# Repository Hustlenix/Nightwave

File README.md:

# Nightwave

Current builder boundary (2026-10-06): target PCB <=90x60 mm, finished device
about <=110x70x25 mm, INR15,000 electronics + PCB/assembly excluding tools.
Final PCB redesign/routing and enclosure CAD are builder-authored. The large
AI reference is not the final design; battery remains unselected. See
[compact requirements](docs/compact-builder-constraints.md), which supersede
older size/budget and final-CAD authoring permissions below.

## PCB checkpoint - 2026-10-06

The AI-authored [KiCad reference project](hardware/kicad/nightwave-reference/README.md)
now has a routed four-layer board, 132 circuit footprints plus three M2
mounting holes, numbered GPIO assignments, and native manufacturing review
exports. See its [validation status](hardware/kicad/nightwave-reference/VALIDATION_STATUS.md)
and [engineering checkpoint](docs/reference-pcb-checkpoint.md) for exact results.
The [downloadable review package](hardware/kicad/Nightwave-AI-Reference-2026-10-06.zip)
includes editable sources, PDF, Gerbers, drill, positions and board STEP.

The [completion ledger](docs/design-completion-status.md) tracks open work.
The [reference firmware profile](docs/reference-board-firmware.md) now matches
the PCB GPIO map and implements TFT output and expander buttons. Typed ERC,
DRC and schematic/board parity pass locally; hardware operation remains untested.

**This is not fabrication or grant-submission approval.** USB source-current
and protection, power-loop/current capacity, complete component procurement,
firmware-to-board integration and enclosure fit remain unresolved. Clean
connectivity/clearance checks are not electrical safety or functional proof.
The builder requested this separate AI-authored reference when their laptop
could not run KiCad; their original starter files remain untouched.

Nightwave is an in-progress, standalone pocket music player for the Pixl “A Music player for the saloon” Trial. It reads user-owned MP3 and PCM/WAV files directly from microSD, with software decoding, physical controls, wired stereo headphones, a speaker, synchronized LRC and Bluetooth output. No phone or streaming service is required. The builder selected ESP32-S3 plus BM83SM1-00TA (BD-14) and Waveshare 24382 non-touch TFT (BD-15). Their hardware drivers, combined GPIO map and battery sizing are not qualified or locked.

> Status (2026-10-03): WAV/MP3 three-task streaming, bench OLED/five-button interaction,
> lyrics/metadata/M3U, modes, bounded seek/resume, sleep timer and versioned
> persistence are implemented for the provisional hardware. The 2026-10-02
> continuation adds an idle-built SD catalog, paged songs/artists/albums and
> bounded PSRAM lookups for filtered browsing/track changes, MP3 duration/sparse
> seek, full-text display interface, BT/power contracts and engineering telemetry;
> [catalog limits](docs/library-index.md) remain explicit. See the
> [expanded-scope checkpoint](docs/engineering-budgets.md) for remaining software.
> Executed [firmware/host CI evidence](docs/software-validation.md) is revision-specific.
> **Funding package is NOT READY:** final power design,
> complete procurement BOM, reviewed enclosure CAD and human reviews are
> missing. An [AI-authored PCB reference](hardware/kicad/nightwave-reference/README.md)
> now exists; its native checks do not constitute fabrication approval or builder authorship.
> No physical playback, runtime, fit, final hardware or tier is claimed.

## Why it exists

The original hardware workflow used builder-authored mentor/reviewer mode;
the separate AI-authored reference above was subsequently requested. **Before
final schematic tasks**, review the selected [Bluetooth architecture](docs/bluetooth-architecture.md)
and [display BD-15](docs/display-selection.md). BD-16 selects
[TCA9535PWR input expansion](docs/input-expansion.md); review its [combined GPIO map](docs/pin-budget.md)
and review the [current power model](docs/current-power-model.md), charger/pack
and complete BOM before the first schematic task. Then use
[builder tasks](docs/builder-tasks.md), [subsystem requirements](docs/schematic-requirements.md)
and [your decision log](docs/builder-decisions.md). AI research and review are
disclosed; final schematic, routing and enclosure must be materially authored
by the builder. The reported Pixl clarification does not mark missing work done.

The product goal is to play the builder's own music offline without a phone,
notifications, subscription or hidden playback module. The builder's personal
motivation and genuine work journal must remain their own account; this README
does not invent a first-person build story.

## Architecture

```text
microSD / FAT
      |
      v
StorageTask -> compressed ring buffer -> DecoderTask -> PCM ring buffer
                                                        |
                                                        v
                                                AudioOutputTask
                                                        |
                                                   I2S + DMA
                                      +-----------------+-----------------+
                                      |                                   |
                                PCM5102A DAC                       MAX98360C amp
                                      |                                   |
                              TPA6132A2 headphone amp                mono speaker
                                      |
                               3.5 mm stereo jack
```

The ESP32 owns file enumeration, storage reads, MP3/WAV decoding, buffering, playback state, I2S output, buttons, UI, settings, diagnostics, and power policy. Nightwave does not use DFPlayer or another module that hides the storage/decode/playback pipeline. The diagram above is the current two-local-output software/bench path. The product requires a third mutually exclusive, rate-qualified I2S branch to BM83SM1-00TA for A2DP source output. Its radio adapter, combined playback router and 22.05/32 kHz conversion are not implemented. Host-tested Bluetooth control/framing contracts do not make that output operational.

The bench prototype uses an available MAX98357A breakout as a functional speaker-path proxy. The current AI-authored KiCad reference uses MAX98357AETE+T (TQFN); MAX98360C in historical candidate documents is not the reference board's fitted amplifier. This remains an unqualified engineering candidate.

## Current implementation

- repository and required engineering-document structure;
- current Pixl/Trial rules verification and honest AI-disclosure strategy;
- datasheet-backed provisional component comparison, BOM, pin budget, power tree, risk register, prototype plan, and decoder study;
- ESP-IDF 6.1 C++ firmware with safe-muted boot, chip/reset/heap/PSRAM diagnostics, debounced five-button logging, 1-bit SDMMC mount/enumeration/benchmarking, I2S DMA output, and a low-level tone test;
- robust host-tested WAV parsing for 16-bit mono/stereo PCM at 22.05/32/44.1/48 kHz, including unknown-chunk skipping and explicit errors;
- three-task WAV/MP3 streaming through a 32 KiB encoded ring and 16,384-frame
  SPSC PCM ring, pause/resume, cancellation, gain ramps and queue/error telemetry;
- SH1106 OLED driver (SSD1306 option), file/folder browser, now-playing, five
  buttons, headphone indicator, no-SD/error screens, sleep and diagnostics;
- bounded LRC, ID3v2.3/v2.4/ID3v1/WAV INFO metadata and local M3U/M3U8 loading;
- SD-backed incremental catalog, 16-row songs/artists/albums views, full indexed
  collection/filter queues, bounded artist/album lookup and checked ordinal-hint
  filter/folder resume; low-memory/over-cap caches use a slower fallback;
- normal/shuffle/repeat-all/repeat-track; accepted-sample lyric clock; WAV direct
  seek and idle-built sparse MP3 seek checkpoints with decoder preroll, safe
  decode-from-start fallback and a 30-minute resume/seek cap;
- versioned checked NVS volume/mode/output/resume/playlist/folder persistence,
  explicit saved-track resume and 15/30/45/60-minute/end-track sleep timers;
- JSON boot/stream/performance/self-test/engineering records, with unmeasured hardware marked;
- injected display frame interface carrying full bounded metadata/LRC strings;
  tested Bluetooth source-state/timeout/backpressure boundary and unknown-safe
  power HAL, without pretending unqualified adapters are operational;
- portable tests for WAV parsing, generated fixtures, ring wrap/full behavior, stereo-to-mono arithmetic, volume scaling, button debounce, and playback state;
- CI definitions for both ESP32-S3 firmware and portable host tests;
- exact Phase 2 prototype BOM, pin-by-pin wiring table, voltage/current plan, deterministic test-media generator, and staged bring-up checklist.

The firmware does **not** prove that a card mounts, a waveform reaches a physical
module, a speaker/headphone produces correct audio, or buffering survives real
card latency. OLED/controller wiring, jack detection and NVS behavior still need
bench validation. Battery reads, power-latch shutdown and automatic SD hotplug
reinitialization are not implemented. Retry/error handling is not a claim that
removing a real card during playback has been tested.

## Controls

The [Trial acceptance matrix](docs/trial-acceptance.md) maps every requirement to
source and missing physical proof. The [runtime recorder](docs/runtime-test.md)
logs sampled elapsed/playback windows and faults; it cannot certify battery life.

Previous/Next navigate the browser or change playing tracks. Play opens a folder
or starts/toggles playback. Volume +/- changes gain. Hold Play for the browser,
hold Previous for the parent folder, hold Volume + for diagnostics, hold Next
for lyrics and hold Volume - for mode/sleep/resume/output settings. First input
after the 30 s display sleep wakes without changing playback.
See [complete controls and limitations](docs/player-controls.md).

## Audio architecture

Helix decodes MP3 in software on ESP32-S3; WAV uses the validated PCM parser.
Storage, decode and I2S have separate tasks. PCM is stereo 16-bit at supported
22.05/32/44.1/48 kHz rates. ID3 skipping and resynchronization are bounded;
unsupported or corrupt media produces a recoverable error. The Class-D path
must select averaged-stereo mono in the reviewed final hardware; headphone
output uses the separate stereo DAC/amp path. Neither path is physically proven.

## Power architecture

USB-C and a protected 1S pack feed a charger/power path; SYS powers the speaker
and a buck-boost supplies 3.3 V. This direction is **provisional**, not a finished
circuit. The [selected-product screening model](docs/current-power-model.md)
calculates MCU, SD, selected TFT, speaker/wired/BT, idle, transients and charging.
Its continuously lit typical speaker case needs an estimated 7.08 Ah for eight
hours under the documented margins; a hypothetical 6.6 Ah gives 7.46 h, not a
passing measurement. Dimming/gating scenarios are conditional, not implemented
power savings. The [historical OLED model](docs/power-budget.md) is superseded.
[Charger timer, source-current and peak-load conflicts](docs/power-assumptions.md)
must be resolved before locking hardware. Estimated runtime is not measured
runtime, and charge-while-play safety is not verified.

## PCB and enclosure

The [current KiCad reference](hardware/kicad/nightwave-reference/README.md)
contains a seven-sheet schematic, placed four-layer board, project-local land
patterns and explicit pin map. Check its [revision-specific validation status](hardware/kicad/nightwave-reference/VALIDATION_STATUS.md)
for actual routing, DRC/parity results and available review exports. The source
is AI-authored at the builder's request, not evidence of human-authored CAD.
It is not fabrication approved. No reviewed editable enclosure, full mechanical
assembly or physical build proof is claimed. See [the reference differences and remaining gates](docs/reference-pcb-checkpoint.md).
An [AI-assisted KiCad starter](hardware/kicad/nightwave-starter/START_HERE.md)
now supplies a root hierarchy, six empty subsystem sheets and a blank board so
the builder can begin quickly. It is scaffolding only: it contains no finished
circuit, footprint assignment, GPIO map, placement or routing and is not funding
evidence by itself.
The board, battery, speaker, display, controls and ports must all have verified
mounting and clearances in the builder-owned design before funding submission.

## BOM

[Preliminary BOM CSV](hardware/BOM.csv): captured-price core subtotal **$53.16**,
including selected BM83 and Waveshare 24382, excluding the pending battery. This is
not a finished BOM total or funding/order cost. USB-C, support parts, PCB,
assembly, enclosure, delivery and taxes also remain excluded/pending. Critical
rows now include package, datasheet, source, footprint and electrical roles;
pending rows are explicit, not approved substitutes. The spreadsheet review
preserved the CSV and checked its selected/pending fields. Older prices remain
dated snapshots; the selected display was checked via official indexed content
2026-10-03 (direct fetch refused; stock/delivery unverified).
No parts have been ordered by this run.

## Build the firmware

Target toolchain: ESP-IDF `v6.1`, target `esp32s3`.

```sh
cd firmware
idf.py set-target esp32s3
idf.py build
```

The development baseline is `ESP32-S3-DevKitC-1-N8R8`; the provisional final module is `ESP32-S3-WROOM-1-N16R8`. Pins and component choices remain provisional until prototype validation.

Use `idf.py -p PORT flash monitor` after building, with the documented DevKit
only and verified wiring. The console adds `play`, `pause`, `resume`, and
`volume` to the bench commands; `wav` remains an alias. Follow
[Phase 3 firmware bring-up](docs/phase3-firmware-bringup.md) before enabling an
output. Production flashing/power instructions depend on the unfinished PCB.

## Load music and build the prototype

Copy supported `.wav` or `.mp3` files to a FAT-formatted microSD, optionally in
folders. Paths must be under 256 bytes; the browser displays at most 128 entries
per folder. No streaming or network is used. Generated test tones are described
in [test media](docs/test-tracks.md). Free-format/MPEG2.5 MP3, unsupported rates,
24-bit WAV and full Unicode display are not implemented features. Bounded WAV
and MP3 seek and shuffle are implemented; their limits and fallback behavior are
documented in [player controls](docs/player-controls.md) and [software evidence](docs/software-validation.md).

For the USB-powered human-assembled prototype, use the
[prototype BOM](hardware/prototype-BOM.csv), [wiring](docs/prototype-wiring.md)
and [bring-up checklist](docs/prototype-bringup.md). Do not connect a lithium
pack or place a final-PCB order using this preliminary package.

## Current validation and funding status

[Software evidence](docs/software-validation.md) separates actual CI runs from
host simulations and pending board measurements. The regression suite exercises
1000 start/cancel/control transitions, corrupt media, fragmented MP3, WAV,
concurrent ring transfers and real folder-navigation logic with fake devices.

[Funding audit](docs/funding-readiness.md),
[current official requirements](docs/pixl-funding-readiness.md),
[builder design/provenance review](docs/human-design-review.md), and
[independent sanity-check packet](docs/sanity-check.md) record the exact gaps.
Project 1200 was inspected in the authenticated builder session on 2026-10-02.
It is a hardware funding draft, with finished-build status unchecked. The Trial
requires local files, real speakers, physical playback/volume controls and a
full-night battery with the achieved runtime stated. Design funding and finished
build evidence are separate stages; see [the current project audit](docs/project-1200-audit.md).
No funding request has been submitted.

Run the [shipping artifact inventory](docs/shipping-audit.md) to expose unresolved
costs and missing design sources. A passing development validator or green form
checkbox does not establish a complete funding design or T4 eligibility.

## Finished-device acceptance

The [finished-device evidence inventory](docs/trial-acceptance.md#finished-device-evidence-inventory)
tracks own-file standalone speaker playback, physical play/pause/skip/volume,
actual full-night speaker battery runtime, final schematic/CAD/STEP, parts/build
instructions, build photos and a real demo video. The pending record is
[trial-evidence.json](measurements/trial-evidence.json); **achieved runtime is
unknown**, not an estimate or a simulated eight-hour result. No demo video exists
yet. Only populate evidence after the corresponding real work and human review.

```sh
python3 tools/check_trial_readiness.py
```

Exit 2 lists missing evidence. Exit 0 only inventories builder-reported evidence
for human review; it never certifies playback, safety, runtime, authorship or Pixl
acceptance. Keep the full [systems scope](docs/trial-acceptance.md) through release;
the hardware integrations must work, not just appear in the feature list.

## Engineering documents

- [Pixl requirements](docs/pixl-requirements.md)
- [Architecture notes](docs/architecture-notes.md)
- [Component comparison](docs/component-comparison.md)
- [Decoder study](docs/decoder-study.md)
- [Decision log](docs/decisions.md)
- [Pin budget](docs/pin-budget.md)
- [Power tree](docs/power-tree.md)
- [Prototype plan](docs/prototype-plan.md)
- [Prototype BOM](hardware/prototype-BOM.csv)
- [Prototype wiring](docs/prototype-wiring.md)
- [Prototype bring-up checklist](docs/prototype-bringup.md)
- [Deterministic test media](docs/test-tracks.md)
- [Phase 3 firmware bring-up](docs/phase3-firmware-bringup.md)
- [Audio buffer analysis](docs/audio-buffer-analysis.md)
- [Headphone prototype options](docs/headphone-prototype-options.md)
- [MP3 integration plan](docs/mp3-integration-plan.md)
- [Risk register](docs/risks.md)
- [Preliminary BOM](hardware/BOM.csv)
- [AI disclosure](docs/ai-disclosure.md)

## Physical validation still required

Direct-SD playback, decoder timing, buffer sizing, audio quality, channel correctness, output power, noise, thermal behavior, current draw, charge-while-play behavior, battery capacity, full-night runtime, PCB manufacturability, and enclosure fit all require physical evidence. The project-defined acceptance test is at least eight hours of continuous speaker playback under a declared profile; the current Pixl Trial itself says “a full night” and requires the achieved runtime to be stated, but does not publish an exact hour count.

## AI disclosure

AI assistance is being used for research synthesis, repository scaffolding, interface design, documentation, and software checks. The builder must understand and materially review the electrical and mechanical design, physically assemble and test the device, maintain honest journals and photos, and obtain a second-person sanity check before hardware submission. Fully AI-generated hardware design files are not acceptable under the current Pixl hardware rules.

## License

Nightwave's original repository content is provided under the MIT License. Third-party libraries keep their own licenses and notices.
The MP3 wrapper's Apache-2.0 license does not relicense the RealNetworks Helix
decoder. Read [dependency provenance and terms](docs/decoder-licenses.md);
notices are preserved in [licenses](licenses/). Original tone fixtures and the
small text font are generated within this repository, not downloaded media.

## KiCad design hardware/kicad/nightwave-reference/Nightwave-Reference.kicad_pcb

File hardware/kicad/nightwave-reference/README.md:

# Nightwave KiCad reference design

This directory is an AI-authored KiCad engineering reference. See `VALIDATION_STATUS.md` for the actual routing/check results of the exported revision. It is unbuilt, unmeasured, and **not approved for fabrication or lithium-cell connection**. It is not evidence of human-authored CAD or Pixl acceptance.

## What is here

- native KiCad 10 hierarchical schematic and four-layer PCB source;
- selected ESP32-S3, BM83, Waveshare TFT, TCA9535, local DAC/headphone/speaker, USB-C, charger, dual regulated rails, protected battery and service/test interfaces;
- exact logical net/GPIO assignments generated from the same source as the PCB;
- BOM and machine-readable design manifest;
- `manufacturing/` review exports generated by KiCad CLI and prominently marked **DO NOT FABRICATE**;
- `reports/` ERC/DRC/netlist and rendered-review evidence.

## Critical stop

Do not order this board yet. An independent reviewer must close `REVIEW_CHECKLIST.md`. Automated routing and clearance/connectivity checks do not establish USB impedance, power-loop stability, current capacity, RF performance, charger safety, manufacturability or enclosure fit. IC pins now have explicit electrical types from manufacturer pin-function tables. ERC checks this model; it does not verify analog behavior or mode-dependent module configuration. The four source flags declare external power/ground and the analog rail after R30, not safety approval.

## Opening tomorrow

Open `Nightwave-Reference.kicad_pro`. Start with the root schematic, then inspect the PCB. The existing `nightwave-starter` project is intentionally separate and unchanged.

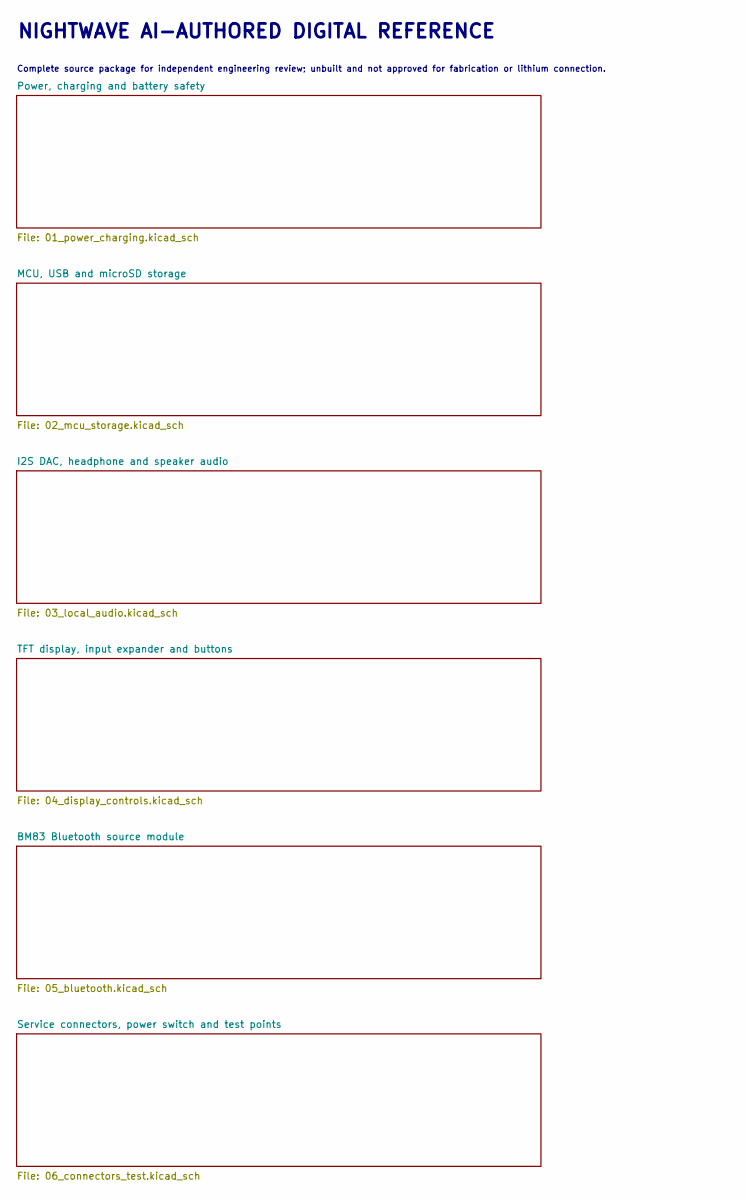
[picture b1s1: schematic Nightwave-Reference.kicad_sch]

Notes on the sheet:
NIGHTWAVE AI-AUTHORED DIGITAL REFERENCE
Complete source package for independent engineering review; unbuilt and not approved for fabrication or lithium connection.

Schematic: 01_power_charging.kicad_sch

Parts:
C1, C2, C7: 10u; C_0603_1608Metric
C3, C4, C5, C6: 22u; C_0603_1608Metric
C8: 4.7u; C_0603_1608Metric
C9: 47n/10V; C_0805_2012Metric
C10: 10u/25V; C_0805_2012Metric
C11, C13: 10u/10V; C_0805_2012Metric
C12, C14: 22u/10V; C_0805_2012Metric
C15: 100n/10V; C_0805_2012Metric
J1: USB4105-GF-A; USB_C_Receptacle_GCT_USB4105-xx-A_16P_TopMnt_Horizontal
J2: BATTERY_CONNECTOR; JST_PH_S2B-PH-K_1x02_P2.00mm_Horizontal
J3: EXTERNAL_10K_NTC; JST_PH_S2B-PH-K_1x02_P2.00mm_Horizontal
L1, L2: 0.47uH XFL4015-471MEC; Coilcraft_XFL4015
L3: 0.7uH XFL4015-701MEC; Coilcraft_XFL4015
R1, R2: 5.1k; R_0603_1608Metric
R3, R4: 4.7k; R_0603_1608Metric
R16: 511k; R_0603_1608Metric
R17, R19: 91k; R_0603_1608Metric
R18: 562k; R_0603_1608Metric
R20: 5.49k; R_0603_1608Metric
R21: 5.23k; R_0603_1608Metric
R22: 30.1k; R_0603_1608Metric
R23: 0; R_0603_1608Metric
U3: BQ25628ERYKR; TI_RYK0018A
U4: TPS22965DSGR; Texas_DSG0008A_WSON-8-1EP_2x2mm_P0.5mm_EP0.9x1.6mm_ThermalV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
U5, U6: TPS63802DLAR; TI_DLA0010A
U7: MAX17048G+T10; TDFN-8-1EP_2x2mm_P0.5mm_EP0.8x1.2mm

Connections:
+3V3: C5.1 (+3V3), C12.1 (+3V3), R3.2 (+3V3), R4.2 (+3V3), R16.1 (+3V3), U5.6 (VOUT); also elsewhere on the board
+3V3_A: C7.1 (+3V3_A); also elsewhere on the board
+3V6_BT: C6.1 (+3V6_BT), C14.1 (+3V6_BT), R18.1 (+3V6_BT), U6.6 (VOUT); also elsewhere on the board
BAT: C2.1 (BAT), C15.1 (BAT), J2.1, U3.8 (BAT), U7.2 (CELL), U7.3 (VDD); also elsewhere on the board
BTST: C9.1 (BTST), U3.1 (BTST)
CHASSIS: J1.SH (SHIELD), R23.1 (CHASSIS)
CHG_INT_N: U3.11 (INT); also elsewhere on the board
CHG_STAT: U3.10 (STAT); also elsewhere on the board
FB_3V3: R16.2 (FB_3V3), R17.1 (FB_3V3), U5.4 (FB)
FB_BT: R18.2 (FB_BT), R19.1 (FB_BT), U6.4 (FB)
FUEL_ALERT_N: U7.5 (ALRT); also elsewhere on the board
GND: C1.2 (GND), C2.2 (GND), C3.2 (GND), C4.2 (GND), C5.2 (GND), C6.2 (GND), C7.2 (GND), C8.2 (GND), C10.2 (GND), C11.2 (GND), C12.2 (GND), C13.2 (GND), C14.2 (GND), C15.2 (GND), J1.A1 (GND), J1.A12 (GND), J1.B1 (GND), J1.B12 (GND), J2.2, J3.2, R1.2 (GND), R2.2 (GND), R17.2 (GND), R19.2 (GND), R20.2 (GND), R22.2 (GND), R23.2 (GND), U3.14 (CE), U3.15 (GND), U4.5 (GND), U4.9 (EP), U5.2 (MODE), U5.3 (AGND), U5.8 (GND), U6.2 (MODE), U6.3 (AGND), U6.8 (GND), U7.1 (CTG), U7.4 (GND), U7.6 (QSTRT), U7.9 (EP); also elsewhere on the board
I2C_SCL: R4.1 (I2C_SCL), U3.13 (SCL), U7.7 (SCL); also elsewhere on the board
I2C_SDA: R3.1 (I2C_SDA), U3.12 (SDA), U7.8 (SDA); also elsewhere on the board
ILIM: R20.1 (ILIM), U3.4 (ILIM)
PGOOD_CHG: U3.3 (PG); also elsewhere on the board
PMID: C10.1 (PMID), U3.17 (PMID)
PWR_GOOD_3V3: U5.5 (PG); also elsewhere on the board
PWR_GOOD_BT: U6.5 (PG); also elsewhere on the board
PWR_SWITCH_ON: U4.3 (ON); also elsewhere on the board
REGN: C8.1 (REGN), U3.2 (REGN)
SW1_3V3: L1.1, U5.9 (L1)
SW1_BT: L2.1, U6.9 (L1)
SW2_3V3: L1.2, U5.7 (L2)
SW2_BT: L2.2, U6.7 (L2)
SW_CHG: C9.2 (SW_CHG), L3.1, U3.16 (SW)
SYS: C3.1 (SYS), L3.2, U3.9 (SYS), U4.1 (VIN), U4.2 (VIN), U4.4 (VBIAS); also elsewhere on the board
TS: J3.1, R21.2 (TS), R22.1 (TS), U3.6 (TS)
TS_BIAS: R21.1 (TS_BIAS), U3.5 (TS_BIAS)
USB_CC1: J1.A5 (CC1), R1.1 (USB_CC1)
USB_CC2: J1.B5 (CC2), R2.1 (USB_CC2)
USB_DM: J1.A7 (D-), J1.B7 (D-); also elsewhere on the board
USB_DP: J1.A6 (D+), J1.B6 (D+); also elsewhere on the board
VBUS5: C1.1 (VBUS5), J1.A4 (VBUS), J1.A9 (VBUS), J1.B4 (VBUS), J1.B9 (VBUS), U3.18 (VBUS); also elsewhere on the board
VSYS_SW: C4.1 (VSYS_SW), C11.1 (VSYS_SW), C13.1 (VSYS_SW), U4.7 (VOUT), U4.8 (VOUT), U5.1 (EN), U5.10 (VIN), U6.1 (EN), U6.10 (VIN); also elsewhere on the board

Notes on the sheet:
Power, charging and battery safety
AI-authored engineering reference. Verify pinout, support values, footprint orientation, lithium safety, RF keepout and assembly before fabrication.

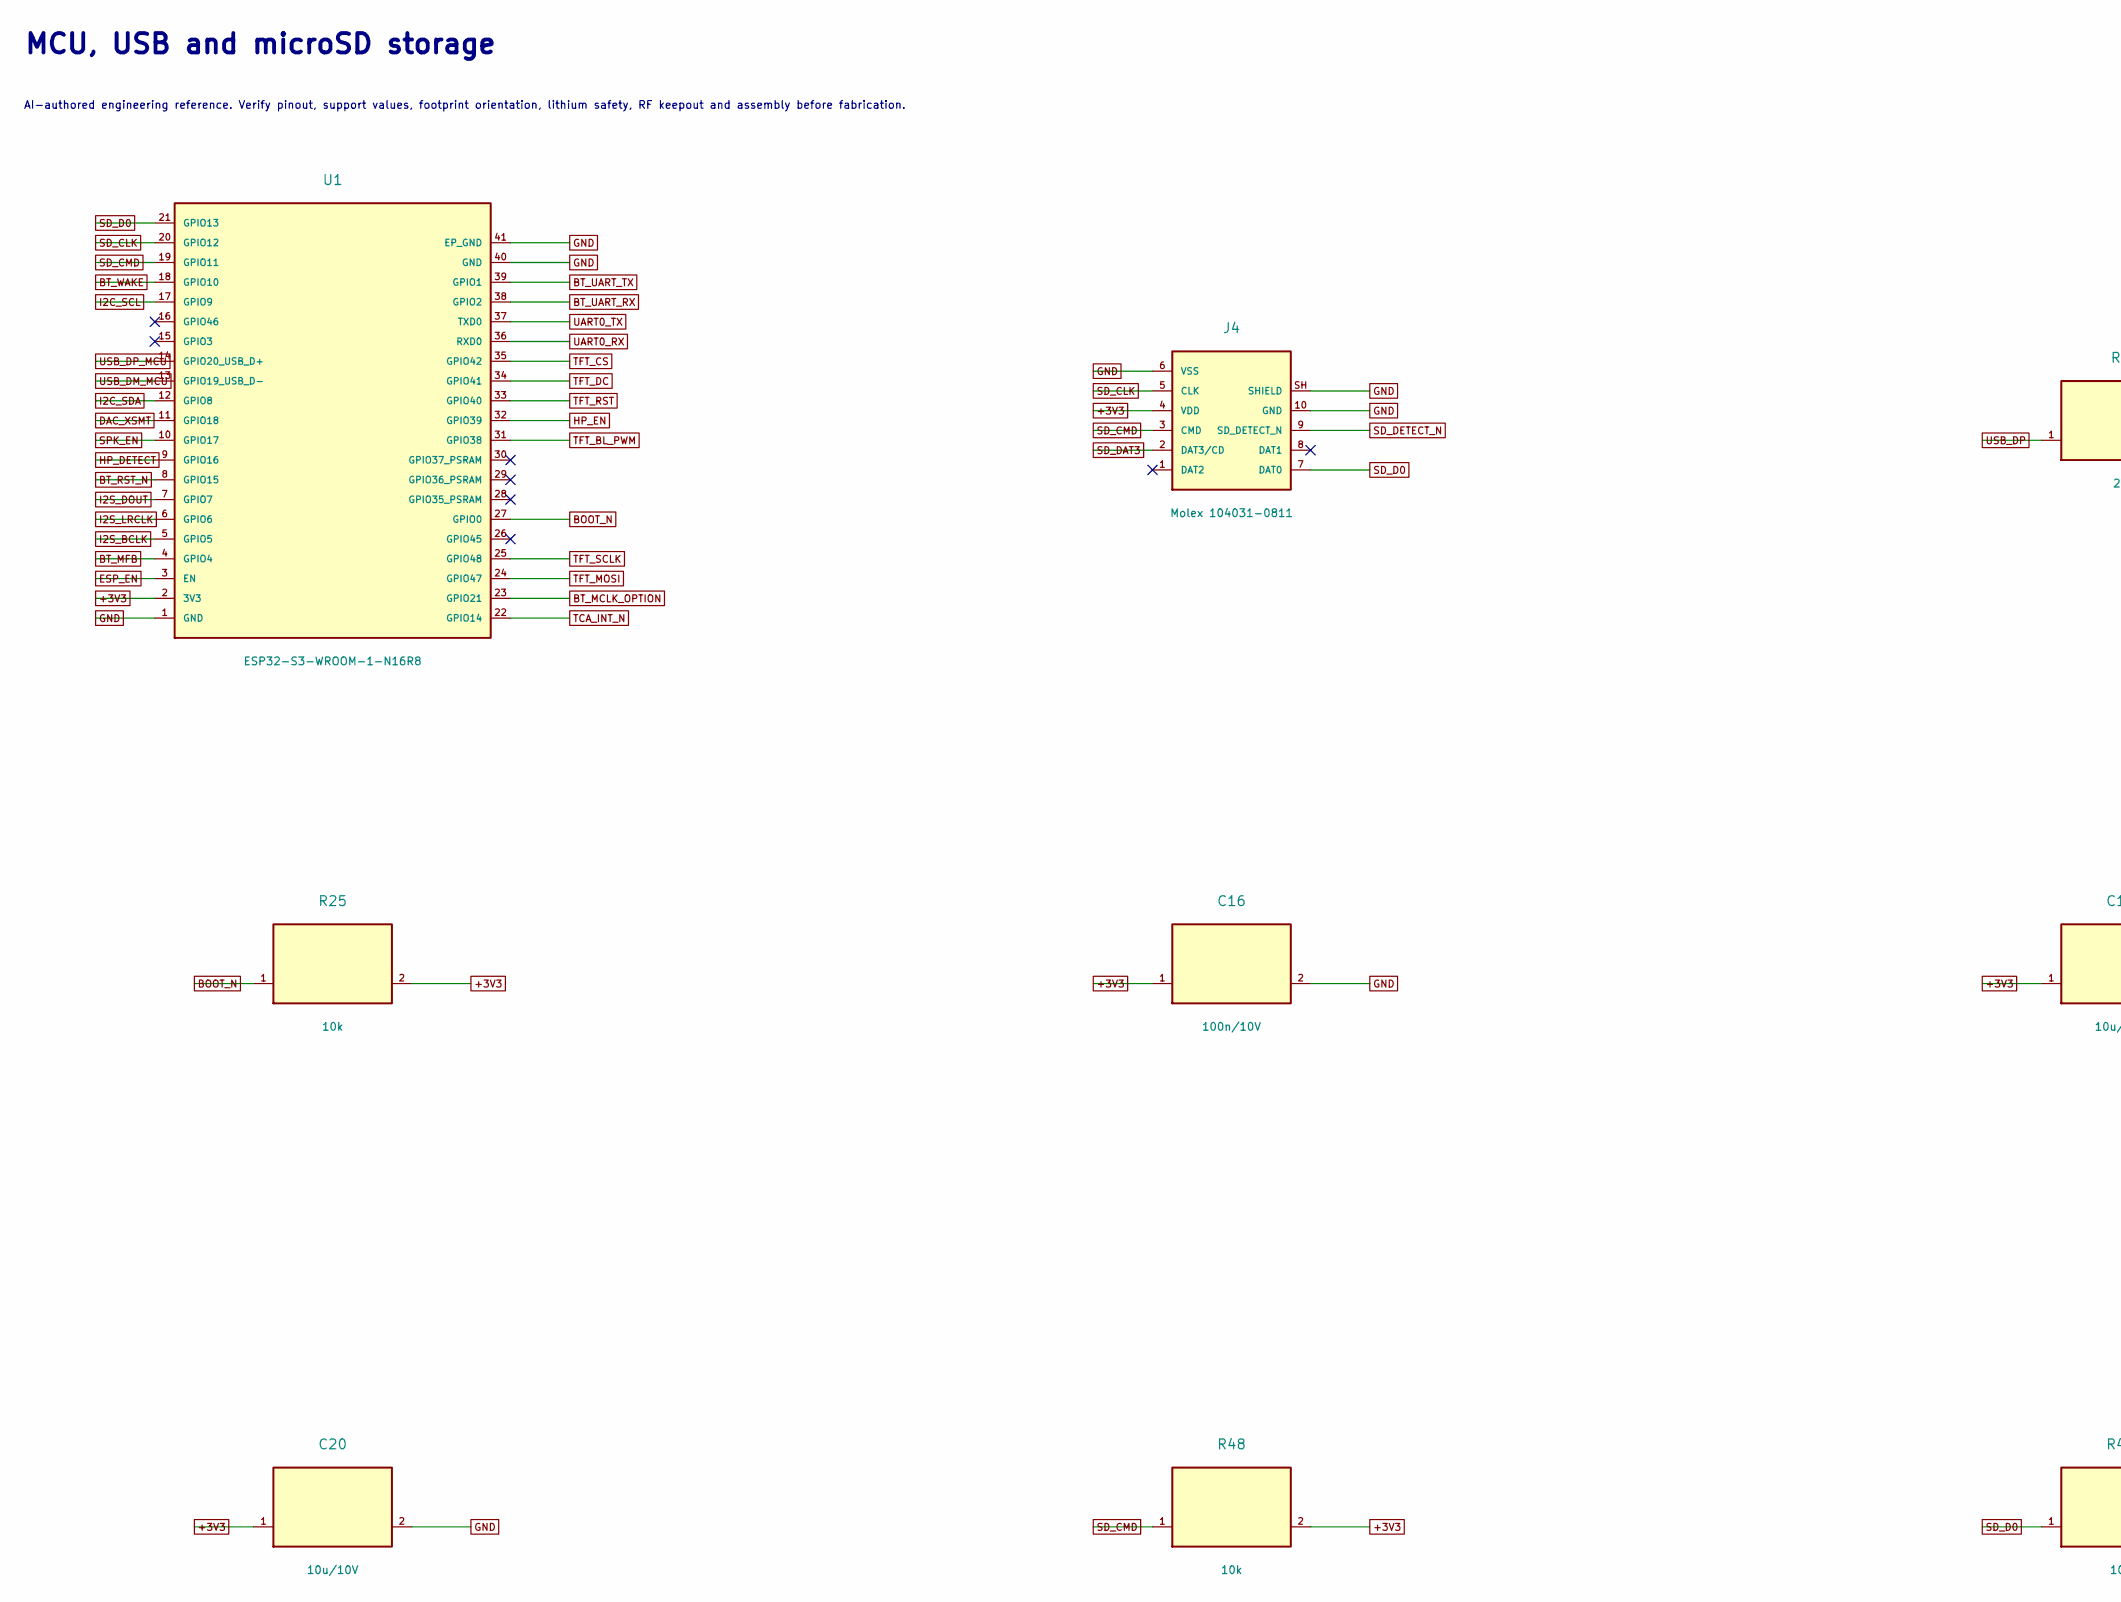
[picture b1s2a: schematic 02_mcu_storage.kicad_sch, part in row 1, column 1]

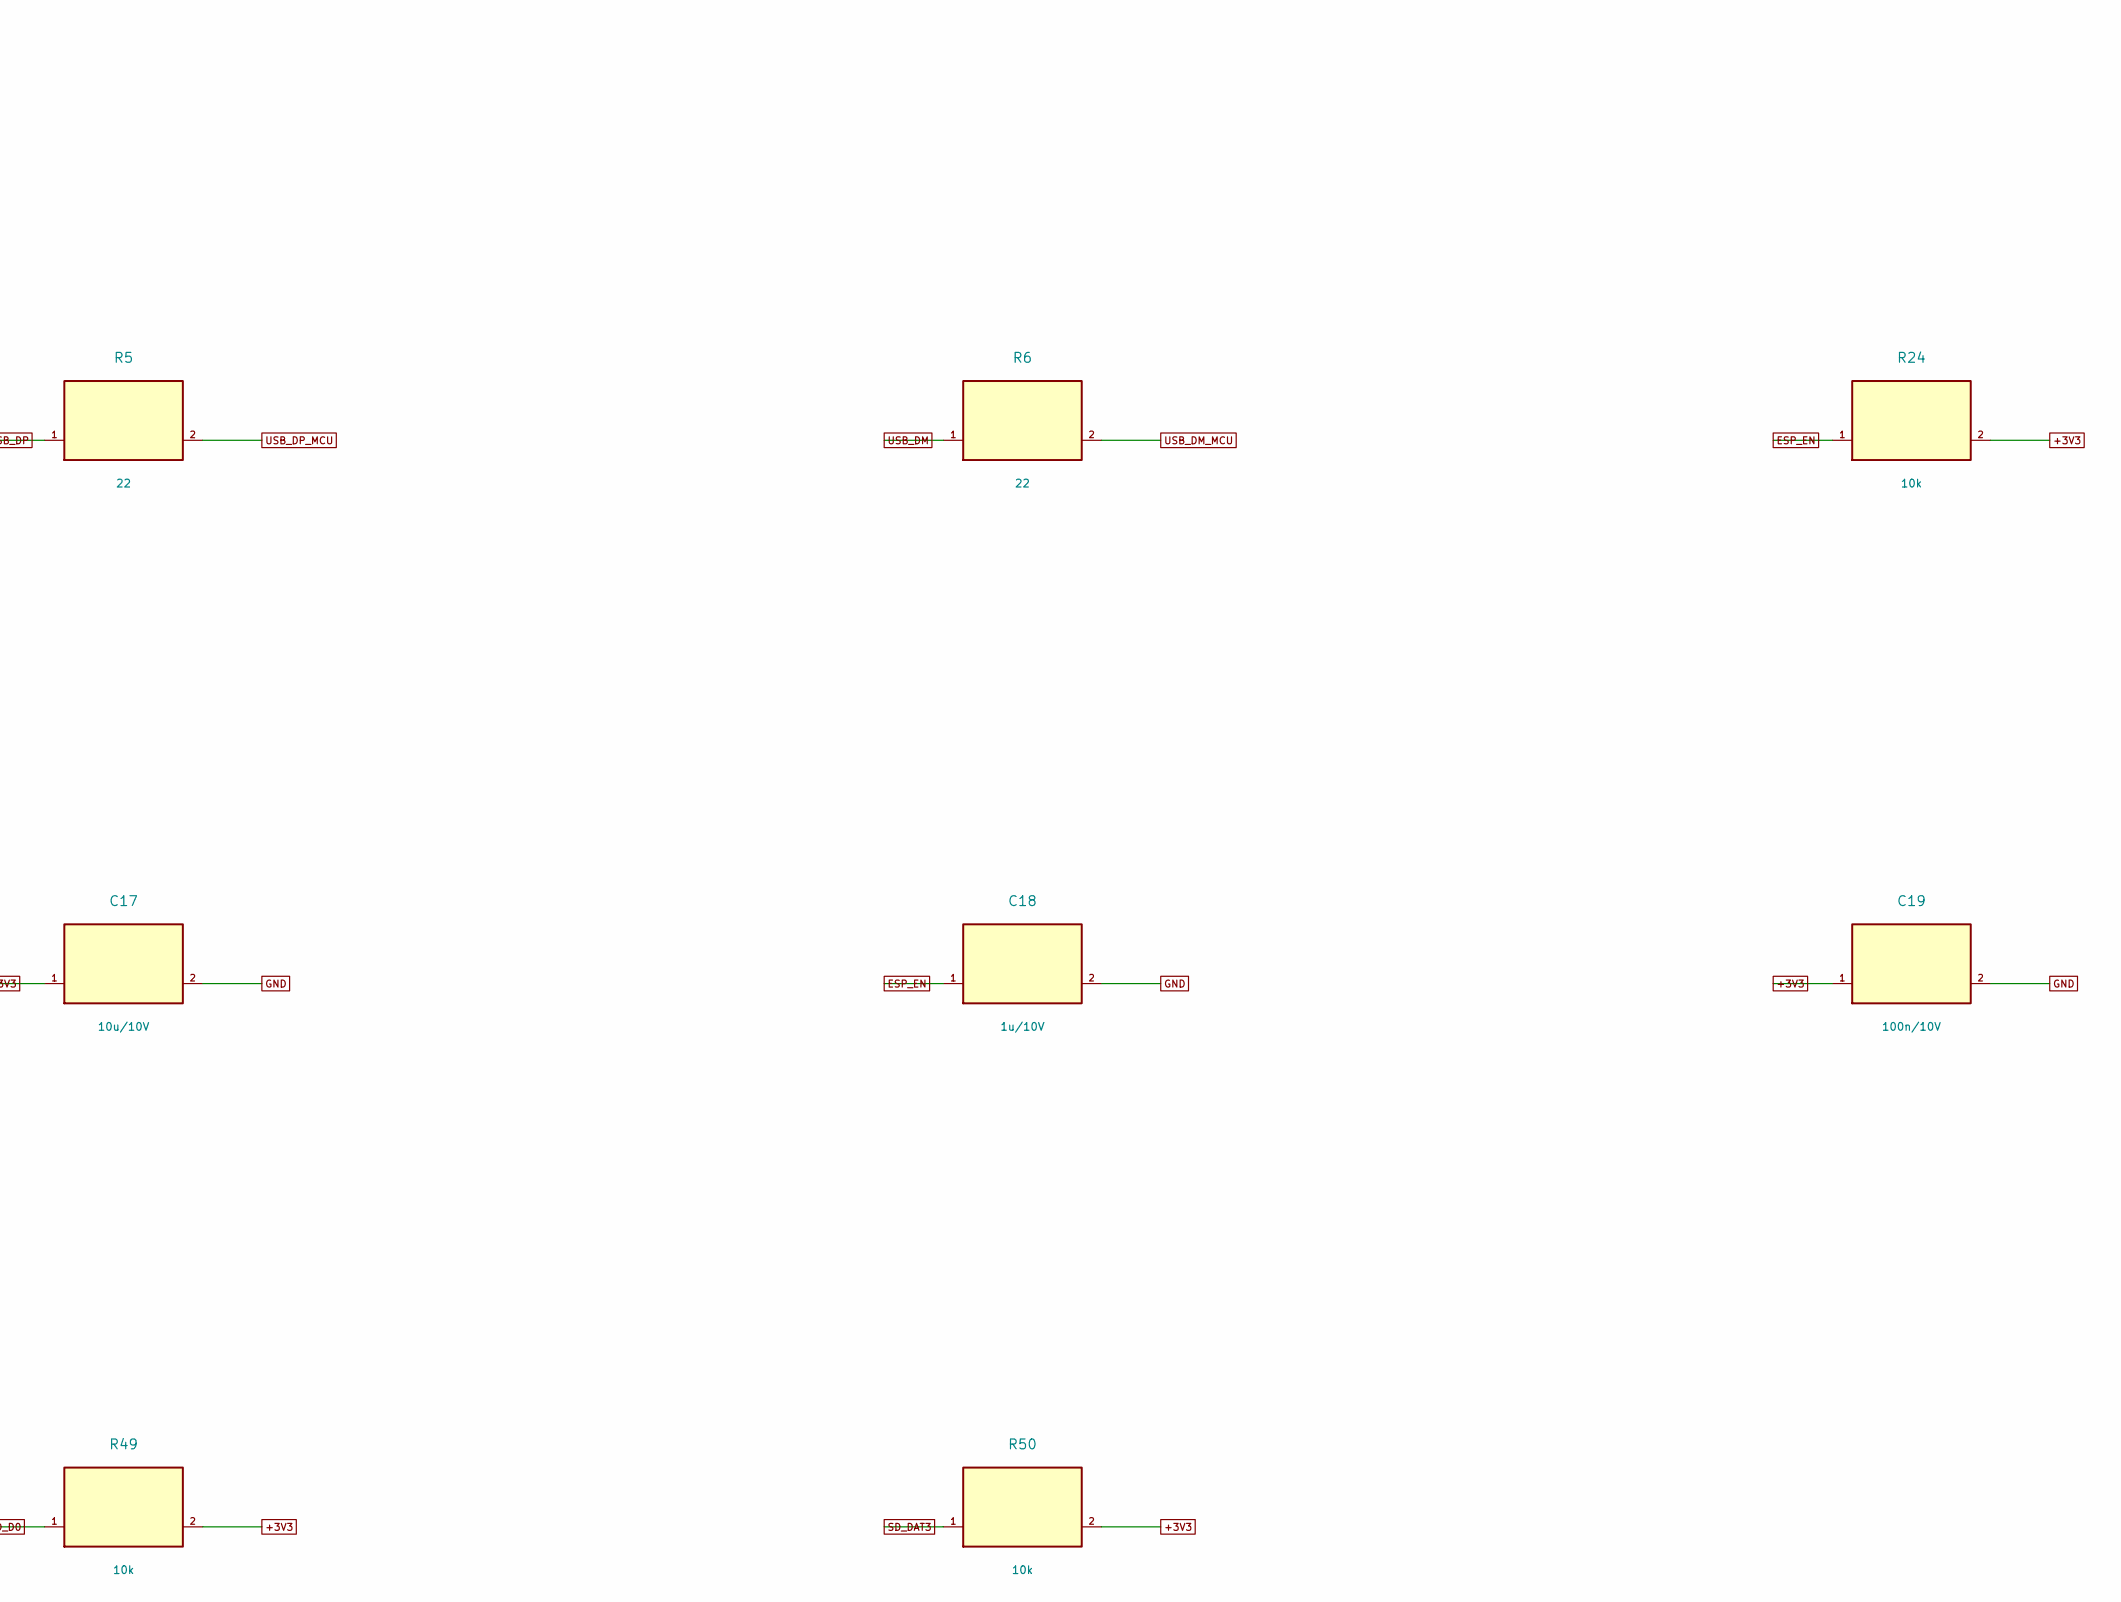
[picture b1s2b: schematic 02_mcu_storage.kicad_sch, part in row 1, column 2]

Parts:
C16, C19: 100n/10V; C_0805_2012Metric
C17, C20: 10u/10V; C_0805_2012Metric
C18: 1u/10V; C_0805_2012Metric
J4: Molex 104031-0811; microSD_HC_Molex_104031-0811
R5, R6: 22; R_0603_1608Metric
R24, R25, R48, R49, R50: 10k; R_0603_1608Metric
U1: ESP32-S3-WROOM-1-N16R8; ESP32-S3-WROOM-1

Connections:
+3V3: C16.1 (+3V3), C17.1 (+3V3), C19.1 (+3V3), C20.1 (+3V3), J4.4 (VDD), R24.2 (+3V3), R25.2 (+3V3), R48.2 (+3V3), R49.2 (+3V3), R50.2 (+3V3), U1.2 (3V3); also elsewhere on the board
BOOT_N: R25.1 (BOOT_N), U1.27 (GPIO0); also elsewhere on the board
BT_MCLK_OPTION: U1.23 (GPIO21); also elsewhere on the board
BT_MFB: U1.4 (GPIO4); also elsewhere on the board
BT_RST_N: U1.8 (GPIO15); also elsewhere on the board
BT_UART_RX: U1.38 (GPIO2); also elsewhere on the board
BT_UART_TX: U1.39 (GPIO1); also elsewhere on the board
BT_WAKE: U1.18 (GPIO10); also elsewhere on the board
DAC_XSMT: U1.11 (GPIO18); also elsewhere on the board
ESP_EN: C18.1 (ESP_EN), R24.1 (ESP_EN), U1.3 (EN); also elsewhere on the board
GND: C16.2 (GND), C17.2 (GND), C18.2 (GND), C19.2 (GND), C20.2 (GND), J4.6 (VSS), J4.10 (GND), J4.SH (SHIELD), U1.1 (GND), U1.40 (GND), U1.41 (EP_GND); also elsewhere on the board
HP_DETECT: U1.9 (GPIO16); also elsewhere on the board
HP_EN: U1.32 (GPIO39); also elsewhere on the board
I2C_SCL: U1.17 (GPIO9); also elsewhere on the board
I2C_SDA: U1.12 (GPIO8); also elsewhere on the board
I2S_BCLK: U1.5 (GPIO5); also elsewhere on the board
I2S_DOUT: U1.7 (GPIO7); also elsewhere on the board
I2S_LRCLK: U1.6 (GPIO6); also elsewhere on the board
SD_CLK: J4.5 (CLK), U1.20 (GPIO12)
SD_CMD: J4.3 (CMD), R48.1 (SD_CMD), U1.19 (GPIO11)
SD_D0: J4.7 (DAT0), R49.1 (SD_D0), U1.21 (GPIO13)
SD_DAT3: J4.2 (DAT3/CD), R50.1 (SD_DAT3)
SD_DETECT_N: J4.9 (SD_DETECT_N); also elsewhere on the board
SPK_EN: U1.10 (GPIO17); also elsewhere on the board
TCA_INT_N: U1.22 (GPIO14); also elsewhere on the board
TFT_BL_PWM: U1.31 (GPIO38); also elsewhere on the board
TFT_CS: U1.35 (GPIO42); also elsewhere on the board
TFT_DC: U1.34 (GPIO41); also elsewhere on the board
TFT_MOSI: U1.24 (GPIO47); also elsewhere on the board
TFT_RST: U1.33 (GPIO40); also elsewhere on the board
TFT_SCLK: U1.25 (GPIO48); also elsewhere on the board
UART0_RX: U1.36 (RXD0); also elsewhere on the board
UART0_TX: U1.37 (TXD0); also elsewhere on the board
USB_DM: R6.1 (USB_DM); also elsewhere on the board
USB_DM_MCU: R6.2 (USB_DM_MCU), U1.13 (GPIO19_USB_D-)
USB_DP: R5.1 (USB_DP); also elsewhere on the board
USB_DP_MCU: R5.2 (USB_DP_MCU), U1.14 (GPIO20_USB_D+)

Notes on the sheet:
MCU, USB and microSD storage
AI-authored engineering reference. Verify pinout, support values, footprint orientation, lithium safety, RF keepout and assembly before fabrication.
